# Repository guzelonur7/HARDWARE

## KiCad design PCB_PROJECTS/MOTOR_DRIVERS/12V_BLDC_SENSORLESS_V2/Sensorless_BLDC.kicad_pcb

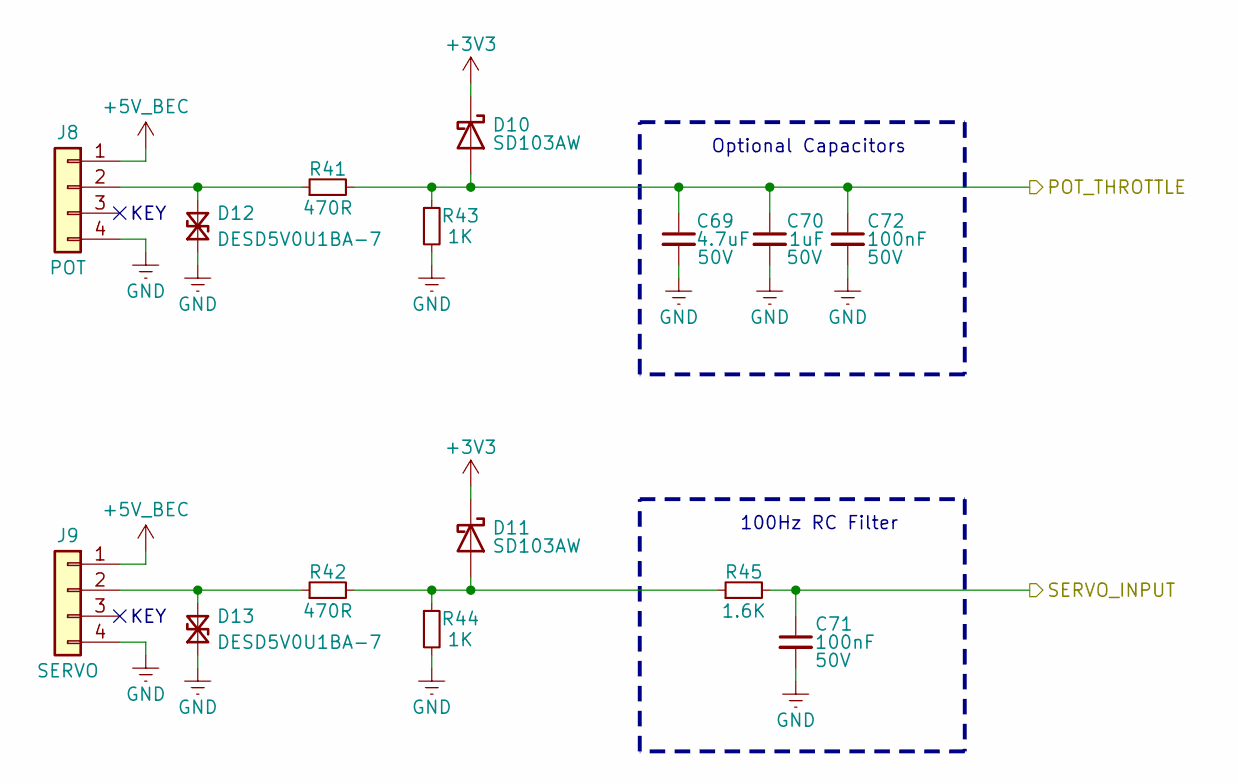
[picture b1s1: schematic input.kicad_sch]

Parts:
C69: 4.7uF; C_0805_2012Metric; Voltage 50V
C70: 1uF; C_0805_2012Metric; Voltage 50V
C71, C72: 100nF; C_0603_1608Metric; Voltage 50V
D10, D11: SD103AW; D_SOD-123
D12, D13: DESD5V0U1BA-7; D_SOD-323
J8: POT; PinHeader_1x04_P2.54mm_Vertical
J9: SERVO; PinHeader_1x04_P2.54mm_Vertical
R41, R42: 470R; R_0603_1608Metric
R43, R44: 1K; R_0603_1608Metric
R45: 1.6K; R_0603_1608Metric

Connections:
+3V3: D10.1 (K), D11.1 (K); also elsewhere on the board
+5V_BEC: J8.1, J9.1; also elsewhere on the board
/Input/POT_THROTTLE: C69.1, C70.1, C72.1, D10.2 (A), R41.2, R43.1; also elsewhere on the board
/Input/SERVO_INPUT: C71.1, R45.2; also elsewhere on the board
GND: C69.2, C70.2, C71.2, C72.2, D12.1 (A1), D13.1 (A1), J8.4, J9.4, R43.2, R44.2; also elsewhere on the board
unnamed: D11.2 (A), R42.2, R44.1, R45.1
unnamed: D12.2 (A2), J8.2, R41.1
unnamed: D13.2 (A2), J9.2, R42.1

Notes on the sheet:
KEY
100Hz RC Filter
Optional Capacitors

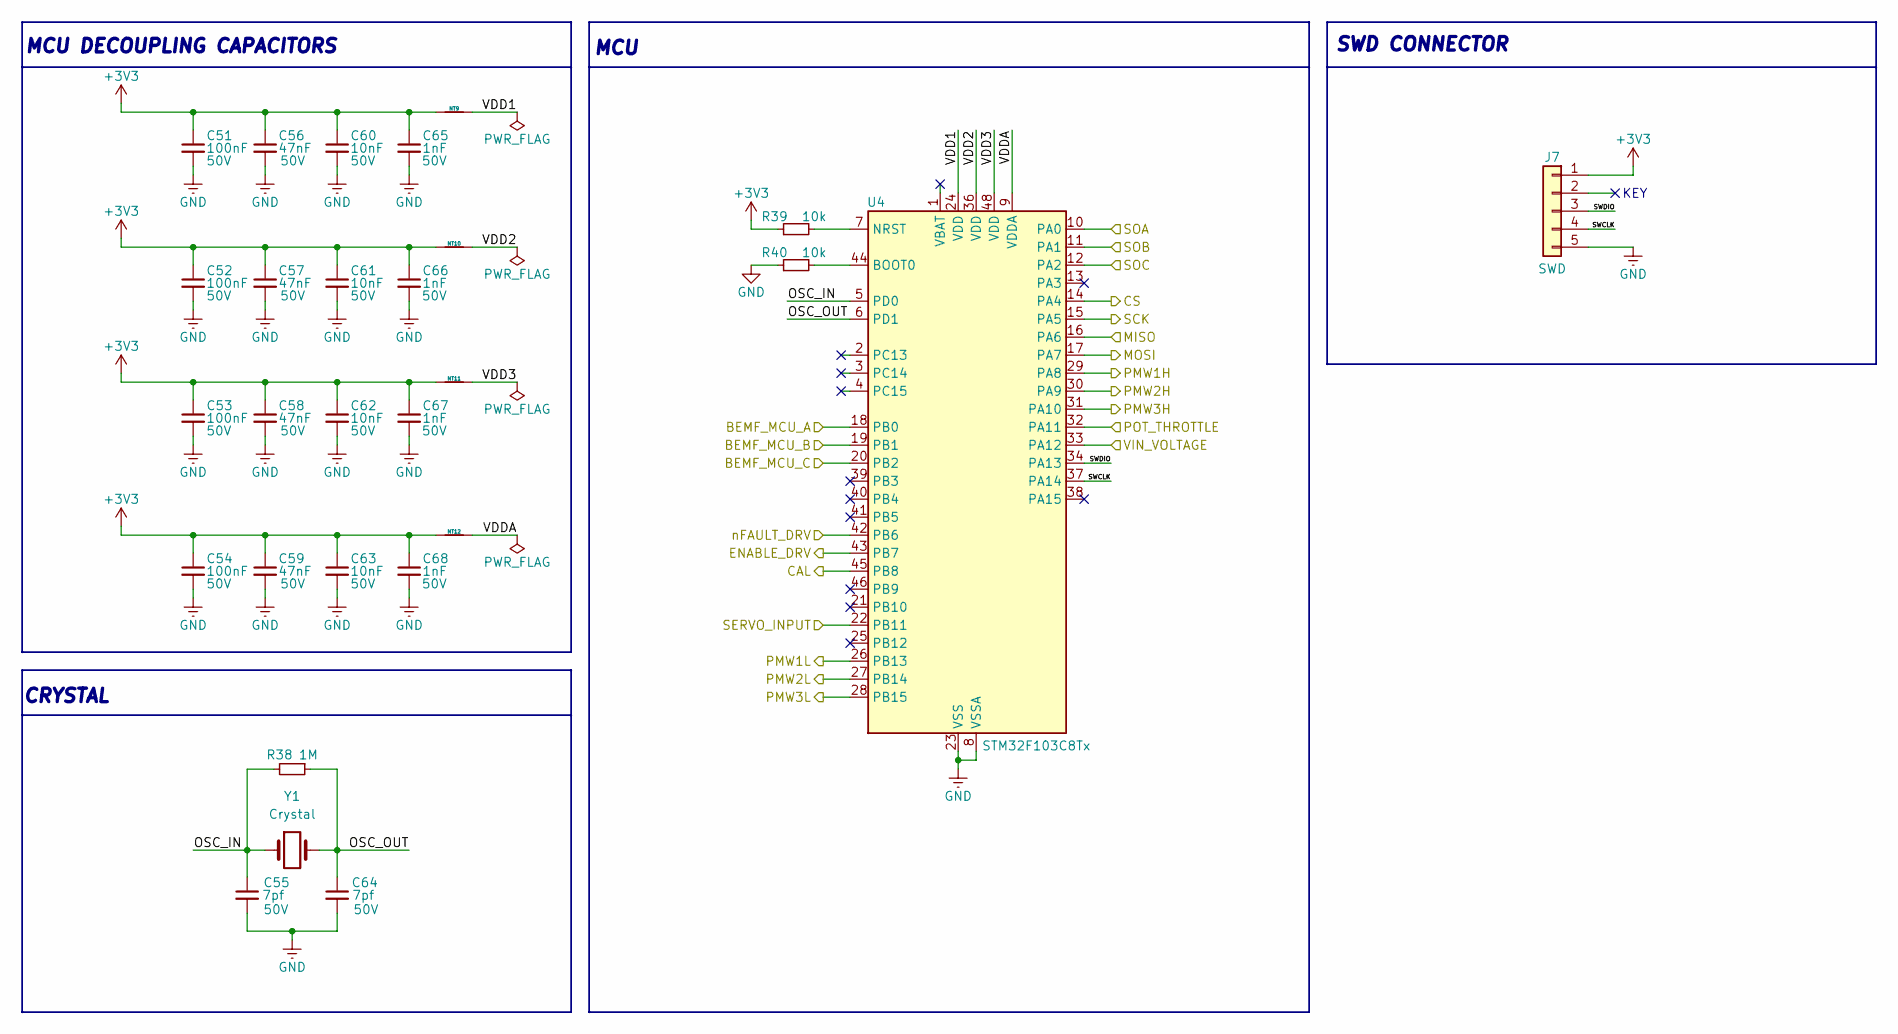
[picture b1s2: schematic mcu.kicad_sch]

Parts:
C51, C52, C53, C54: 100nF; C_0603_1608Metric; Voltage 50V
C55, C64: 7pf; C_0603_1608Metric
C56, C57, C58, C59: 47nF; C_0603_1608Metric; Voltage 50V
C60, C61, C62, C63: 10nF; C_0603_1608Metric; Voltage 50V
C65, C66, C67, C68: 1nF; C_0603_1608Metric; Voltage 50V
J7: SWD; PinHeader_1x05_P2.54mm_Vertical
NT9, NT10, NT11, NT12: NetTie_2; NetTie-2_SMD_Pad0.5mm
R38: 1M; R_0805_2012Metric
R39, R40: 10k; R_0603_1608Metric
U4: STM32F103C8Tx; LQFP-48_7x7mm_P0.5mm
Y1: Crystal; Crystal_SMD_TXC_7A-2Pin_5x3.2mm

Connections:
+3V3: C51.1, C52.1, C53.1, C54.1, C56.1, C57.1, C58.1, C59.1, C60.1, C61.1, C62.1, C63.1, C65.1, C66.1, C67.1, C68.1, J7.1, NT9.1, NT10.1, NT11.1, NT12.1, R39.1; also elsewhere on the board
/A: U4.18 (PB0); also elsewhere on the board
/B: U4.19 (PB1); also elsewhere on the board
/C: U4.20 (PB2); also elsewhere on the board
/Gate Driver/CAL: U4.45 (PB8); also elsewhere on the board
/Gate Driver/CS: U4.14 (PA4); also elsewhere on the board
/Gate Driver/ENABLE: U4.43 (PB7); also elsewhere on the board
/Gate Driver/INHA: U4.29 (PA8); also elsewhere on the board
/Gate Driver/INHB: U4.30 (PA9); also elsewhere on the board
/Gate Driver/INHC: U4.31 (PA10); also elsewhere on the board
/Gate Driver/INLA: U4.26 (PB13); also elsewhere on the board
/Gate Driver/INLB: U4.27 (PB14); also elsewhere on the board
/Gate Driver/INLC: U4.28 (PB15); also elsewhere on the board
/Gate Driver/MISO: U4.16 (PA6); also elsewhere on the board
/Gate Driver/MOSI: U4.17 (PA7); also elsewhere on the board
/Gate Driver/SCK: U4.15 (PA5); also elsewhere on the board
/Gate Driver/SOA: U4.10 (PA0); also elsewhere on the board
/Gate Driver/SOB: U4.11 (PA1); also elsewhere on the board
/Gate Driver/SOC: U4.12 (PA2); also elsewhere on the board
/Gate Driver/nFAULT: U4.42 (PB6); also elsewhere on the board
/Input/POT_THROTTLE: U4.32 (PA11); also elsewhere on the board
/Input/SERVO_INPUT: U4.22 (PB11); also elsewhere on the board
/MCU/OSC_IN: C55.1, R38.2, U4.5 (PD0), Y1.1
/MCU/OSC_OUT: C64.1, R38.1, U4.6 (PD1), Y1.2
/MCU/SWCLK: J7.4, U4.37 (PA14)
/MCU/SWDIO: J7.3, U4.34 (PA13)
/MCU/VDD1: NT9.2, U4.24 (VDD)
/MCU/VDD2: NT10.2, U4.36 (VDD)
/MCU/VDD3: NT11.2, U4.48 (VDD)
/MCU/VDDA: NT12.2, U4.9 (VDDA)
/MCU/VIN_VOLTAGE: U4.33 (PA12); also elsewhere on the board
GND: C51.2, C52.2, C53.2, C54.2, C55.2, C56.2, C57.2, C58.2, C59.2, C60.2, C61.2, C62.2, C63.2, C64.2, C65.2, C66.2, C67.2, C68.2, J7.5, R40.1, U4.8 (VSSA), U4.23 (VSS), U4.35 (VSS), U4.47 (VSS); also elsewhere on the board
unnamed: R40.2, U4.44 (BOOT0)
unnamed: R39.2, U4.7 (NRST)

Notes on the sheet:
KEY
CRYSTAL
MCU
SWD CONNECTOR
MCU DECOUPLING CAPACITORS

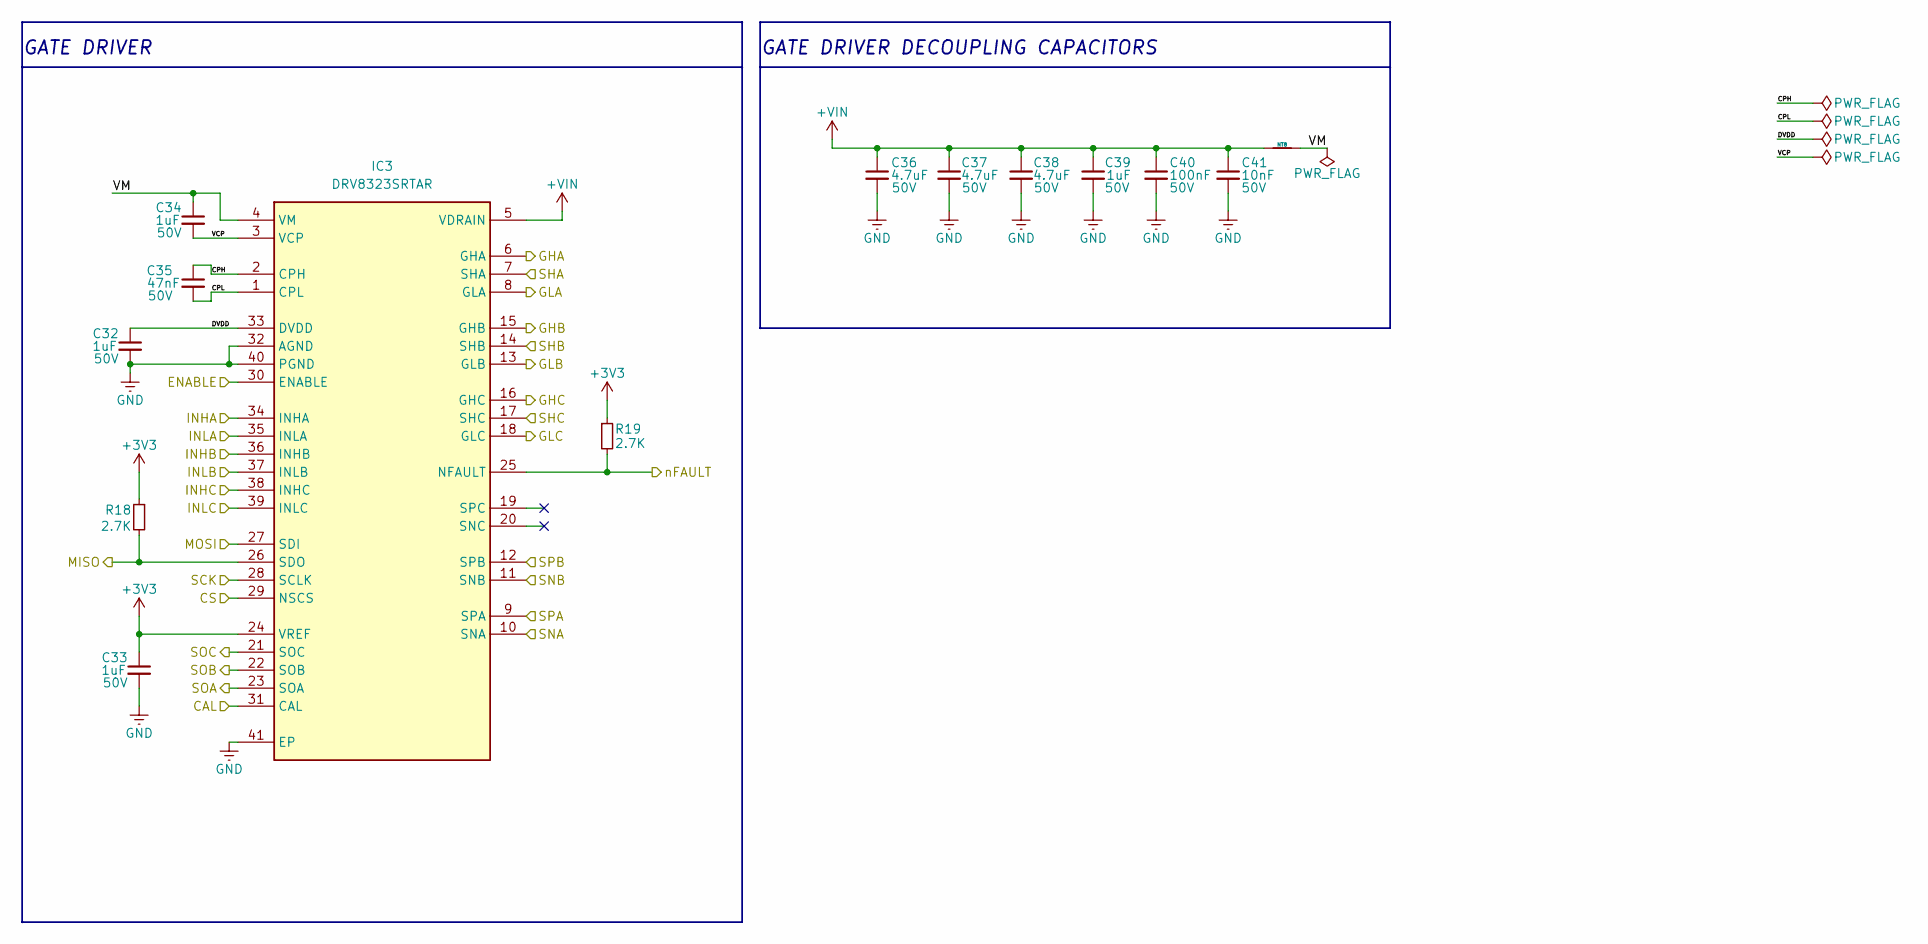
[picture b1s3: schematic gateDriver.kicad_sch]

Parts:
C32, C33, C34, C39: 1uF; C_0805_2012Metric; Voltage 50V
C35: 47nF; C_0603_1608Metric; Voltage 50V
C36, C37, C38: 4.7uF; C_0805_2012Metric; Voltage 50V
C40: 100nF; C_0603_1608Metric; Voltage 50V
C41: 10nF; C_0603_1608Metric; Voltage 50V
IC3: DRV8323SRTAR; WQFN-40
NT8: NetTie_2; NetTie-2_SMD_Pad0.5mm
R18, R19: 2.7K; R_0805_2012Metric

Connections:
+3V3: C33.1, IC3.24 (VREF), R18.1, R19.1; also elsewhere on the board
+VIN: C36.1, C37.1, C38.1, C39.1, C40.1, C41.1, IC3.5 (VDRAIN), NT8.1; also elsewhere on the board
/Gate Driver/CAL: IC3.31 (CAL); also elsewhere on the board
/Gate Driver/CPH: C35.1, IC3.2 (CPH)
/Gate Driver/CPL: C35.2, IC3.1 (CPL)
/Gate Driver/CS: IC3.29 (NSCS); also elsewhere on the board
/Gate Driver/DVDD: C32.1, IC3.33 (DVDD)
/Gate Driver/ENABLE: IC3.30 (ENABLE); also elsewhere on the board
/Gate Driver/GHA: IC3.6 (GHA); also elsewhere on the board
/Gate Driver/GHB: IC3.15 (GHB); also elsewhere on the board
/Gate Driver/GHC: IC3.16 (GHC); also elsewhere on the board
/Gate Driver/GLA: IC3.8 (GLA); also elsewhere on the board
/Gate Driver/GLB: IC3.13 (GLB); also elsewhere on the board
/Gate Driver/GLC: IC3.18 (GLC); also elsewhere on the board
/Gate Driver/INHA: IC3.34 (INHA); also elsewhere on the board
/Gate Driver/INHB: IC3.36 (INHB); also elsewhere on the board
/Gate Driver/INHC: IC3.38 (INHC); also elsewhere on the board
/Gate Driver/INLA: IC3.35 (INLA); also elsewhere on the board
/Gate Driver/INLB: IC3.37 (INLB); also elsewhere on the board
/Gate Driver/INLC: IC3.39 (INLC); also elsewhere on the board
/Gate Driver/MISO: IC3.26 (SDO), R18.2; also elsewhere on the board
/Gate Driver/MOSI: IC3.27 (SDI); also elsewhere on the board
/Gate Driver/SCK: IC3.28 (SCLK); also elsewhere on the board
/Gate Driver/SHA: IC3.7 (SHA); also elsewhere on the board
/Gate Driver/SHB: IC3.14 (SHB); also elsewhere on the board
/Gate Driver/SHC: IC3.17 (SHC); also elsewhere on the board
/Gate Driver/SNA: IC3.10 (SNA); also elsewhere on the board
/Gate Driver/SNB: IC3.11 (SNB); also elsewhere on the board
/Gate Driver/SOA: IC3.23 (SOA); also elsewhere on the board
/Gate Driver/SOB: IC3.22 (SOB); also elsewhere on the board
/Gate Driver/SOC: IC3.21 (SOC); also elsewhere on the board
/Gate Driver/SPA: IC3.9 (SPA); also elsewhere on the board
/Gate Driver/SPB: IC3.12 (SPB); also elsewhere on the board
/Gate Driver/VCP: C34.2, IC3.3 (VCP)
/Gate Driver/VM: C34.1, IC3.4 (VM), NT8.2
/Gate Driver/nFAULT: IC3.25 (NFAULT), R19.2; also elsewhere on the board
GND: C32.2, C33.2, C36.2, C37.2, C38.2, C39.2, C40.2, C41.2, IC3.32 (AGND), IC3.40 (PGND), IC3.41 (EP); also elsewhere on the board

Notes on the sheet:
GATE DRIVER
GATE DRIVER DECOUPLING CAPACITORS

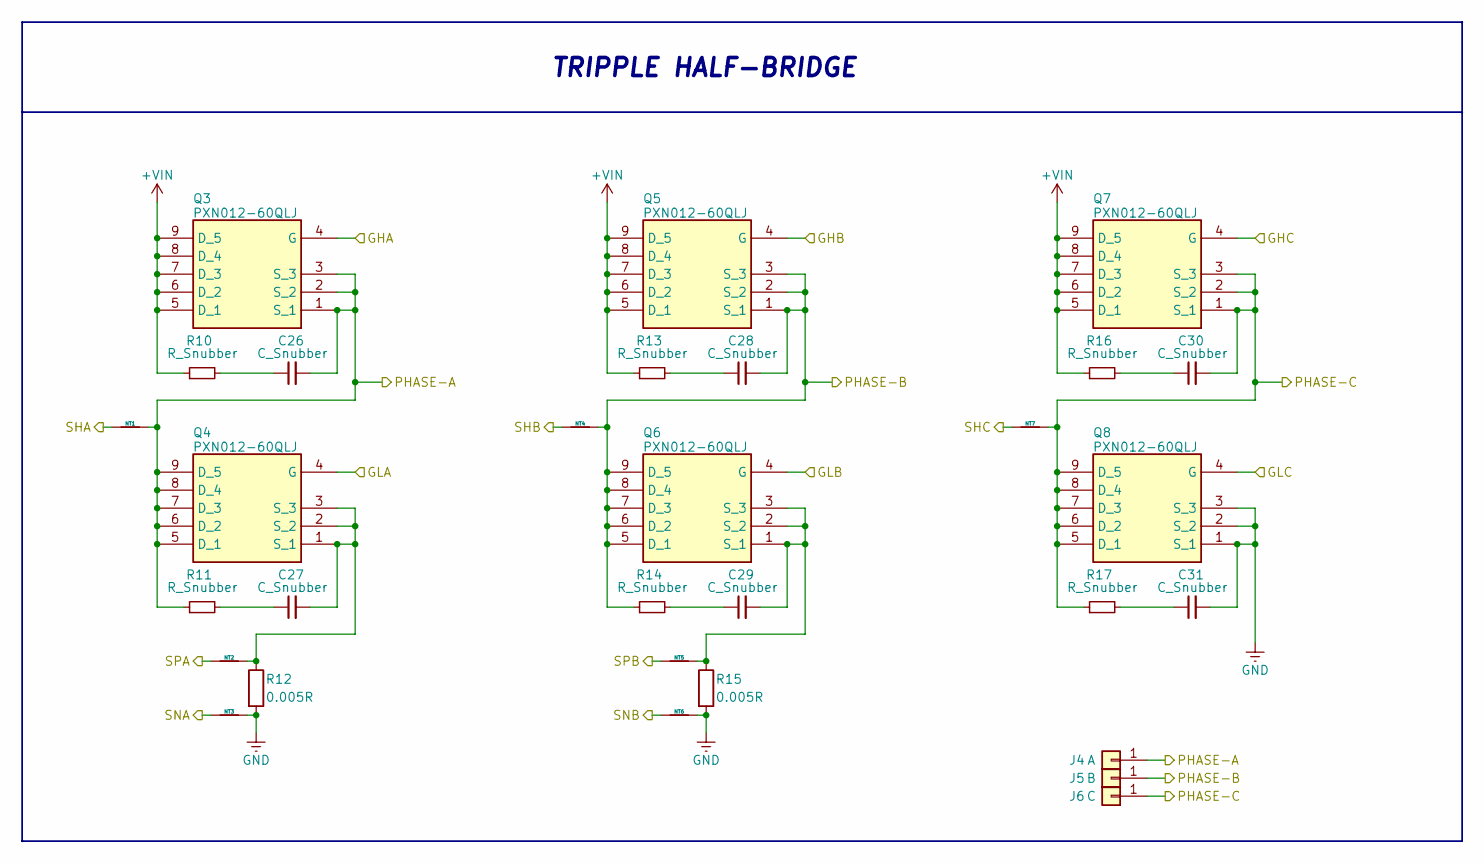
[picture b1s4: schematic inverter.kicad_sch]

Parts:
C26, C27, C28, C29, C30, C31: C_Snubber; C_0603_1608Metric
J4: A; TestPoint_Plated_Hole_D2.0mm
J5: B; TestPoint_Plated_Hole_D2.0mm
J6: C; TestPoint_Plated_Hole_D2.0mm
NT1, NT2, NT3, NT4, NT5, NT6, NT7: NetTie_2; NetTie-2_SMD_Pad0.5mm
Q3, Q4, Q5, Q6, Q7, Q8: PXN012-60QLJ; MLPAK33
R10, R11, R13, R14, R16, R17: R_Snubber; R_0805_2012Metric
R12, R15: 0.005R; R_0612_1632Metric

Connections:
+VIN: Q3.5 (D_1), Q3.6 (D_2), Q3.7 (D_3), Q3.8 (D_4), Q3.9 (D_5), Q5.5 (D_1), Q5.6 (D_2), Q5.7 (D_3), Q5.8 (D_4), Q5.9 (D_5), Q7.5 (D_1), Q7.6 (D_2), Q7.7 (D_3), Q7.8 (D_4), Q7.9 (D_5), R10.1, R13.1, R16.1; also elsewhere on the board
/BEMF Input/PHASE-A: C26.2, J4.1, NT1.2, Q3.1 (S_1), Q3.2 (S_2), Q3.3 (S_3), Q4.5 (D_1), Q4.6 (D_2), Q4.7 (D_3), Q4.8 (D_4), Q4.9 (D_5), R11.1; also elsewhere on the board
/BEMF Input/PHASE-B: C28.2, J5.1, NT4.2, Q5.1 (S_1), Q5.2 (S_2), Q5.3 (S_3), Q6.5 (D_1), Q6.6 (D_2), Q6.7 (D_3), Q6.8 (D_4), Q6.9 (D_5), R14.1; also elsewhere on the board
/BEMF Input/PHASE-C: C30.2, J6.1, NT7.2, Q7.1 (S_1), Q7.2 (S_2), Q7.3 (S_3), Q8.5 (D_1), Q8.6 (D_2), Q8.7 (D_3), Q8.8 (D_4), Q8.9 (D_5), R17.1; also elsewhere on the board
/Gate Driver/GHA: Q3.4 (G); also elsewhere on the board
/Gate Driver/GHB: Q5.4 (G); also elsewhere on the board
/Gate Driver/GHC: Q7.4 (G); also elsewhere on the board
/Gate Driver/GLA: Q4.4 (G); also elsewhere on the board
/Gate Driver/GLB: Q6.4 (G); also elsewhere on the board
/Gate Driver/GLC: Q8.4 (G); also elsewhere on the board
/Gate Driver/SHA: NT1.1; also elsewhere on the board
/Gate Driver/SHB: NT4.1; also elsewhere on the board
/Gate Driver/SHC: NT7.1; also elsewhere on the board
/Gate Driver/SNA: NT3.1; also elsewhere on the board
/Gate Driver/SNB: NT6.1; also elsewhere on the board
/Gate Driver/SPA: NT2.1; also elsewhere on the board
/Gate Driver/SPB: NT5.1; also elsewhere on the board
GND: C31.2, NT3.2, NT6.2, Q8.1 (S_1), Q8.2 (S_2), Q8.3 (S_3), R12.2, R15.2; also elsewhere on the board
unnamed: C26.1, R10.2
unnamed: C27.1, R11.2
unnamed: C28.1, R13.2
unnamed: C29.1, R14.2
unnamed: C30.1, R16.2
unnamed: C31.1, R17.2
unnamed: C27.2, NT2.2, Q4.1 (S_1), Q4.2 (S_2), Q4.3 (S_3), R12.1
unnamed: C29.2, NT5.2, Q6.1 (S_1), Q6.2 (S_2), Q6.3 (S_3), R15.1

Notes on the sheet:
TRIPPLE HALF-BRIDGE

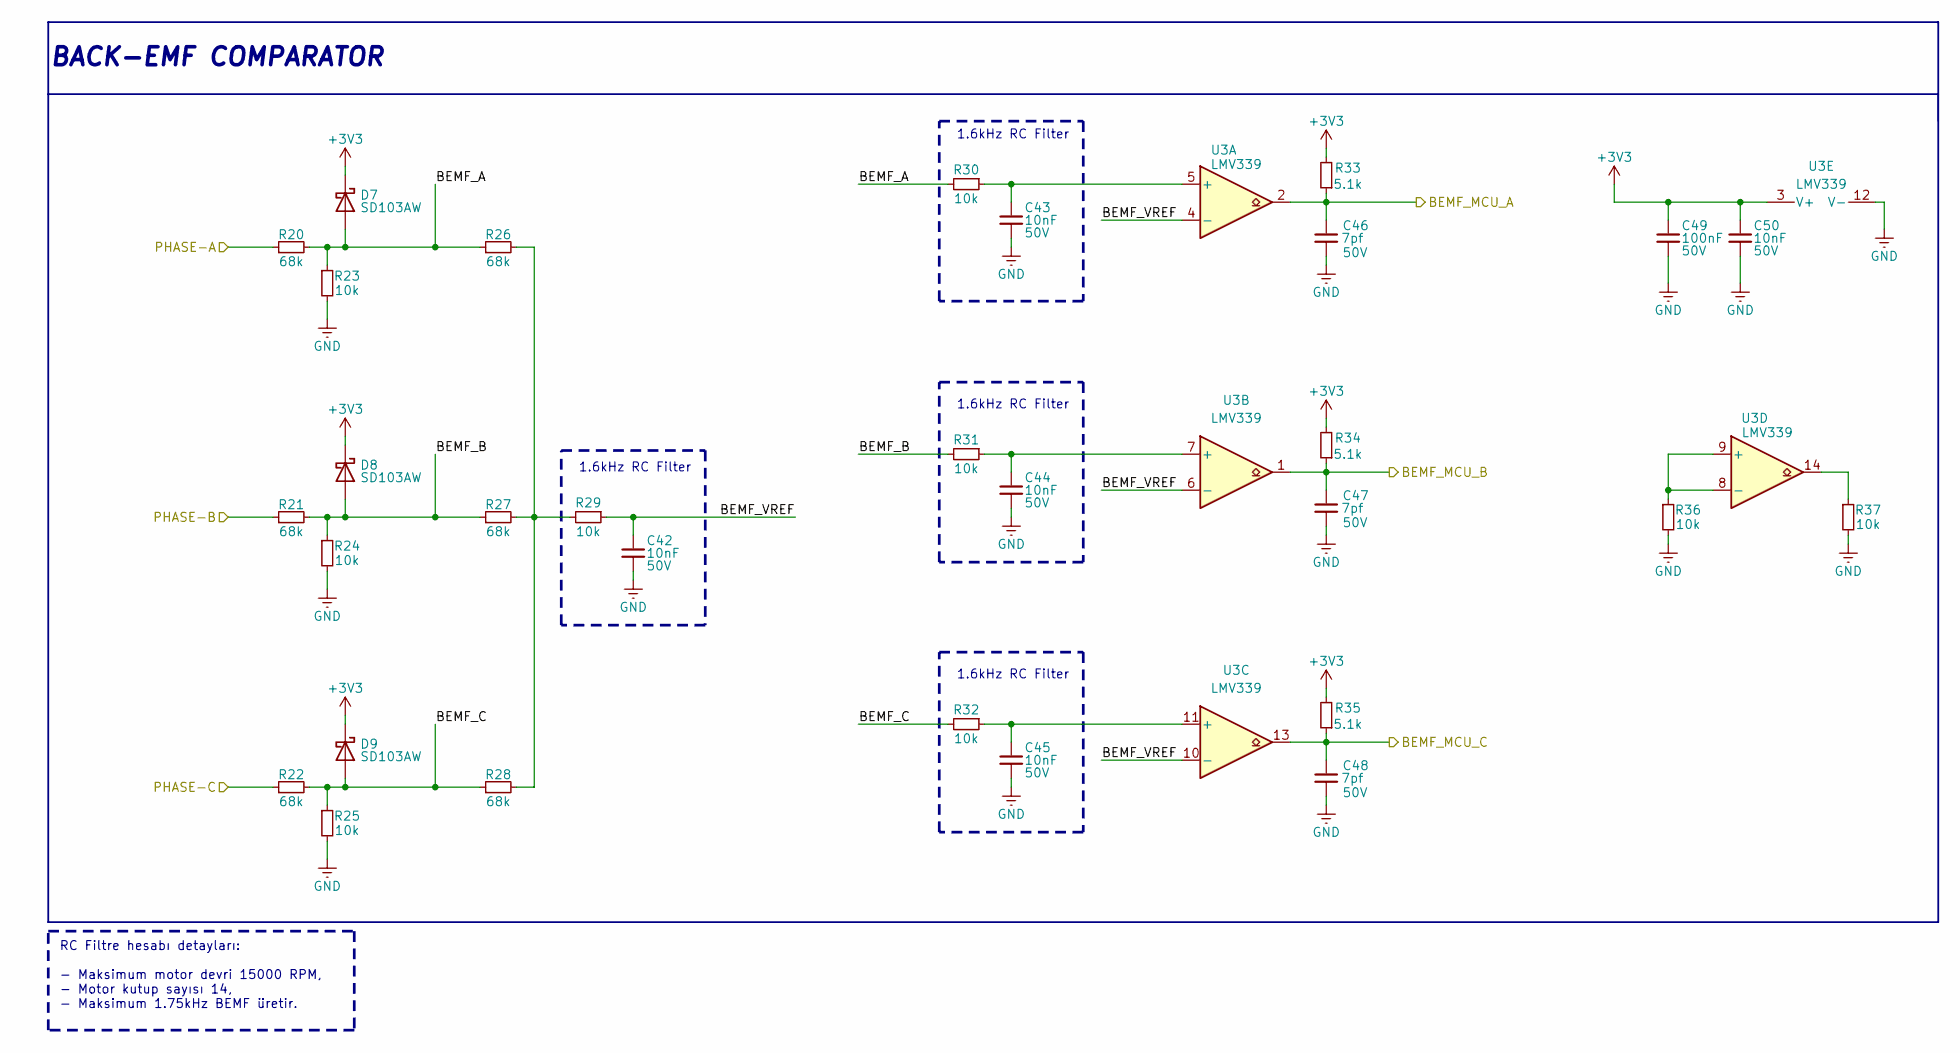
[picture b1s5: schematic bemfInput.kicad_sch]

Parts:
C42, C43, C44, C45, C50: 10nF; C_0603_1608Metric; Voltage 50V
C46, C47, C48: 7pf; C_0603_1608Metric
C49: 100nF; C_0603_1608Metric; Voltage 50V
D7, D8, D9: SD103AW; D_SOD-123
R20, R21, R22, R26, R27, R28: 68k; R_0603_1608Metric
R23, R24, R25, R29, R30, R31, R32, R36, R37: 10k; R_0603_1608Metric
R33, R34, R35: 5.1k; C_0603_1608Metric
U3: LMV339; SO-14_3.9x8.65mm_P1.27mm

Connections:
+3V3: C49.1, C50.1, D7.1 (K), D8.1 (K), D9.1 (K), R33.2, R34.2, R35.2, U3.3 (V+); also elsewhere on the board
/A: C46.1, R33.1, U3.2; also elsewhere on the board
/B: C47.1, R34.1, U3.1; also elsewhere on the board
/BEMF Input/BEMF_A: D7.2 (A), R20.2, R23.1, R26.1, R30.2
/BEMF Input/BEMF_B: D8.2 (A), R21.2, R24.1, R27.1, R31.2
/BEMF Input/BEMF_C: D9.2 (A), R22.2, R25.1, R28.1, R32.2
/BEMF Input/BEMF_VREF: C42.1, R29.1, U3.4 (-), U3.6 (-), U3.10 (-)
/BEMF Input/PHASE-A: R20.1; also elsewhere on the board
/BEMF Input/PHASE-B: R21.1; also elsewhere on the board
/BEMF Input/PHASE-C: R22.1; also elsewhere on the board
/C: C48.1, R35.1, U3.13; also elsewhere on the board
GND: C42.2, C43.2, C44.2, C45.2, C46.2, C47.2, C48.2, C49.2, C50.2, R23.2, R24.2, R25.2, R36.2, R37.2, U3.12 (V-); also elsewhere on the board
unnamed: R26.2, R27.2, R28.2, R29.2
unnamed: R37.1, U3.14
unnamed: C43.1, R30.1, U3.5 (+)
unnamed: C44.1, R31.1, U3.7 (+)
unnamed: C45.1, R32.1, U3.11 (+)
unnamed: R36.1, U3.8 (-), U3.9 (+)

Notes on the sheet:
1.6kHz RC Filter
RC Filtre hesabı detayları: - Maksimum motor devri 15000 RPM, - Motor kutup sayısı 14, - Maksimum 1.75kHz BEMF üretir.
BACK-EMF COMPARATOR

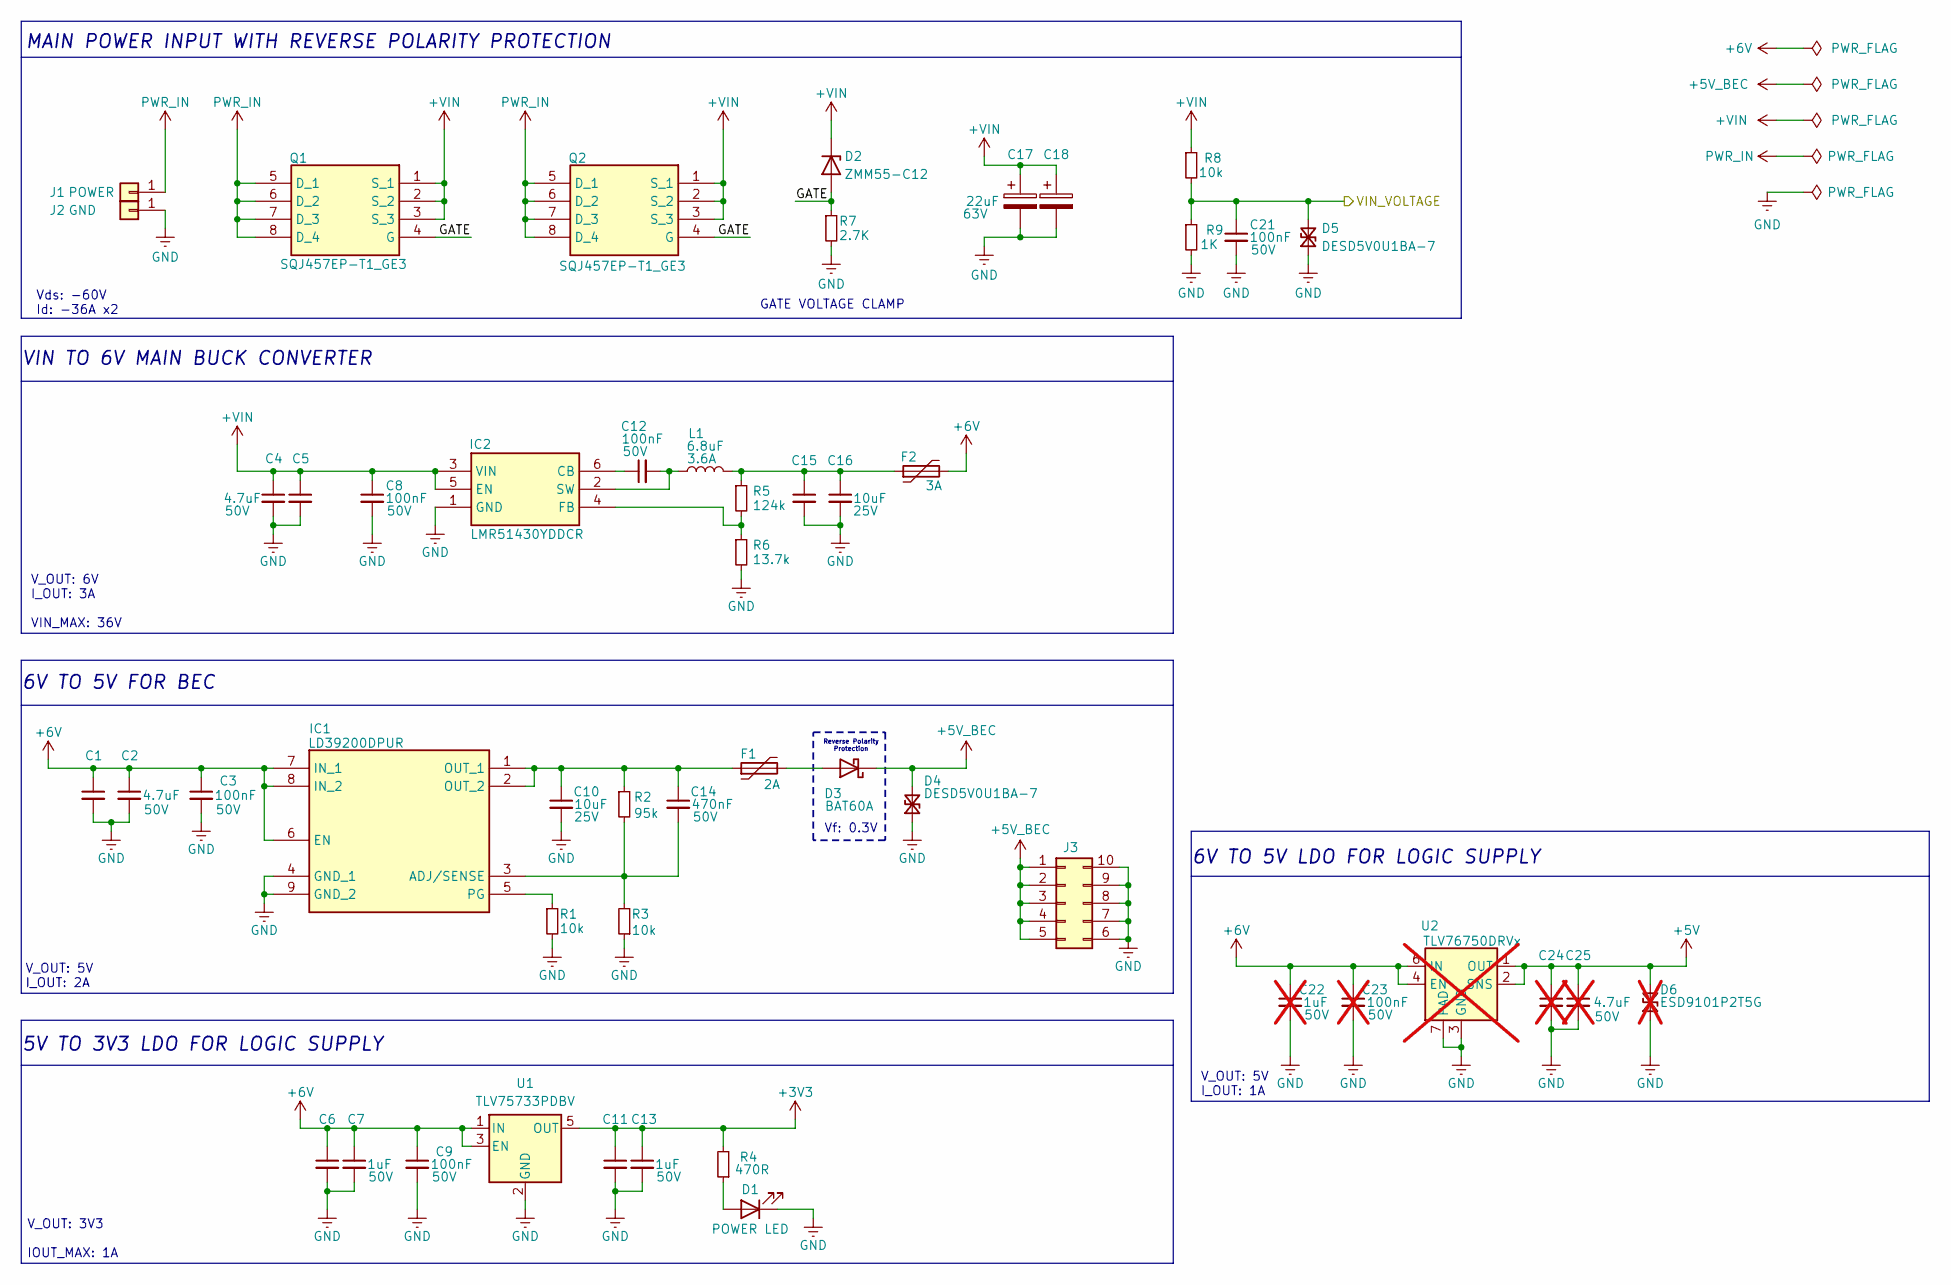
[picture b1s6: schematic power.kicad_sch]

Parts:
C1, C2, C4, C5: 4.7uF; C_0805_2012Metric; Voltage 50V
C3, C8, C9, C12, C21: 100nF; C_0603_1608Metric; Voltage 50V
C6, C7, C11, C13: 1uF; C_0805_2012Metric; Voltage 50V
C10, C15, C16: 10uF; C_0805_2012Metric; Voltage 25V
C14: 470nF; C_0805_2012Metric; Voltage 50V
C17, C18: 22uF; CP_Radial_D5.0mm_P2.50mm
C22: 1uF; C_0805_2012Metric; Voltage 50V; not fitted
C23: 100nF; C_0603_1608Metric; Voltage 50V; not fitted
C24, C25: 4.7uF; C_0805_2012Metric; Voltage 50V; not fitted
D1: POWER LED; LED_0603_1608Metric
D2: ZMM55-C12; D_MiniMELF
D3: BAT60A; D_SOD-323
D4, D5: DESD5V0U1BA-7; D_SOD-323
D6: ESD9101P2T5G; D_SOD-323; not fitted
F1: 2A; Fuse_0805_2012Metric
F2: 3A; Fuse_1206_3216Metric
IC1: LD39200DPUR; DFN-8-1EP_4x4mm_P0.8mm_EP2.3x3.24mm; Manufacturer_Part_Number LD39200DPUR
IC2: LMR51430YDDCR; SOT23-THIN-6
J1: POWER; MountingHole_2.2mm_M2_DIN965_Pad
J2: GND; MountingHole_2.2mm_M2_DIN965_Pad
J3: Conn_02x05_Counter_Clockwise; PinHeader_2x05_P2.54mm_Vertical
L1: 6.8uF; L_Wurth_WE-LQSH-4020
Q1, Q2: SQJ457EP-T1_GE3; PowerPAK-SO-8-4
R1, R3, R8: 10k; R_0603_1608Metric
R2: 95k; R_0603_1608Metric
R4: 470R; R_0603_1608Metric
R5: 124k; R_0603_1608Metric
R6: 13.7k; R_0603_1608Metric
R7: 2.7K; R_0805_2012Metric
R9: 1K; R_0603_1608Metric
U1: TLV75733PDBV; SOT-23-5
U2: TLV76750DRVx; WSON-6-1EP_2x2mm_P0.65mm_EP1x1.6mm_ThermalVias; not fitted

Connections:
+3V3: C11.1, C13.1, R4.2, U1.5 (OUT); also elsewhere on the board
+5V: C24.1, C25.1, D6.2 (A2), U2.1 (OUT), U2.2 (SNS)
+5V_BEC: D3.1 (K), D4.2 (A2), J3.1, J3.2, J3.3, J3.4, J3.5; also elsewhere on the board
+6V: C1.1, C2.1, C3.1, C6.1, C7.1, C9.1, C22.1, C23.1, F2.2, IC1.6 (EN), IC1.7 (IN_1), IC1.8 (IN_2), U1.1 (IN), U1.3 (EN), U2.4 (EN), U2.6 (IN)
+VIN: C4.1, C5.1, C8.1, C17.1, C18.1, D2.1 (K), IC2.3 (VIN), IC2.5 (EN), Q1.1 (S_1), Q1.2 (S_2), Q1.3 (S_3), Q2.1 (S_1), Q2.2 (S_2), Q2.3 (S_3), R8.1; also elsewhere on the board
/MCU/VIN_VOLTAGE: C21.1, D5.2 (A2), R8.2, R9.1; also elsewhere on the board
/Power/GATE: D2.2 (A), Q1.4 (G), Q2.4 (G), R7.1
GND: C1.2, C2.2, C3.2, C4.2, C5.2, C6.2, C7.2, C8.2, C9.2, C10.2, C11.2, C13.2, C15.2, C16.2, C17.2, C18.2, C21.2, C22.2, C23.2, C24.2, C25.2, D1.1 (K), D4.1 (A1), D5.1 (A1), D6.1 (A1), IC1.4 (GND_1), IC1.9 (GND_2), IC2.1 (GND), J2.1, J3.6, J3.7, J3.8, J3.9, J3.10, R1.2, R3.1, R6.2, R7.2, R9.2, U1.2 (GND), U2.3 (GND), U2.5 (GND), U2.7 (PAD); also elsewhere on the board
unnamed: C15.1, C16.1, F2.1, L1.2, R5.1
unnamed: D1.2 (A), R4.1
unnamed: D3.2 (A), F1.2
unnamed: C14.2, IC1.3 (ADJ/SENSE), R2.2, R3.2
unnamed: C10.1, C14.1, F1.1, IC1.1 (OUT_1), IC1.2 (OUT_2), R2.1
unnamed: IC1.5 (PG), R1.1
unnamed: C12.1, IC2.6 (CB)
unnamed: IC2.4 (FB), R5.2, R6.1
unnamed: C12.2, IC2.2 (SW), L1.1
PWR_IN: J1.1, Q1.5 (D_1), Q1.6 (D_2), Q1.7 (D_3), Q1.8 (D_4), Q2.5 (D_1), Q2.6 (D_2), Q2.7 (D_3), Q2.8 (D_4)

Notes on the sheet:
V_OUT: 5V I_OUT: 1A
V_OUT: 6V I_OUT: 3A VIN_MAX: 36V
V_OUT: 3V3 IOUT_MAX: 1A
Reverse Polarity Protection
5V TO 3V3 LDO FOR LOGIC SUPPLY
Vds: -60V Id: -36A x2
MAIN POWER INPUT WITH REVERSE POLARITY PROTECTION
Vf: 0.3V
V_OUT: 5V I_OUT: 2A
6V TO 5V FOR BEC
GATE VOLTAGE CLAMP
6V TO 5V LDO FOR LOGIC SUPPLY
VIN TO 6V MAIN BUCK CONVERTER

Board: 6 copper layers, 168 parts (0 on the bottom side), 91 nets, no tracks yet.
